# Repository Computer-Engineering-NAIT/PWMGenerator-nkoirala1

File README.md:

# PWMGenerator-nkoirala1
Practical Electronic - CMPE2150 - PCB Project

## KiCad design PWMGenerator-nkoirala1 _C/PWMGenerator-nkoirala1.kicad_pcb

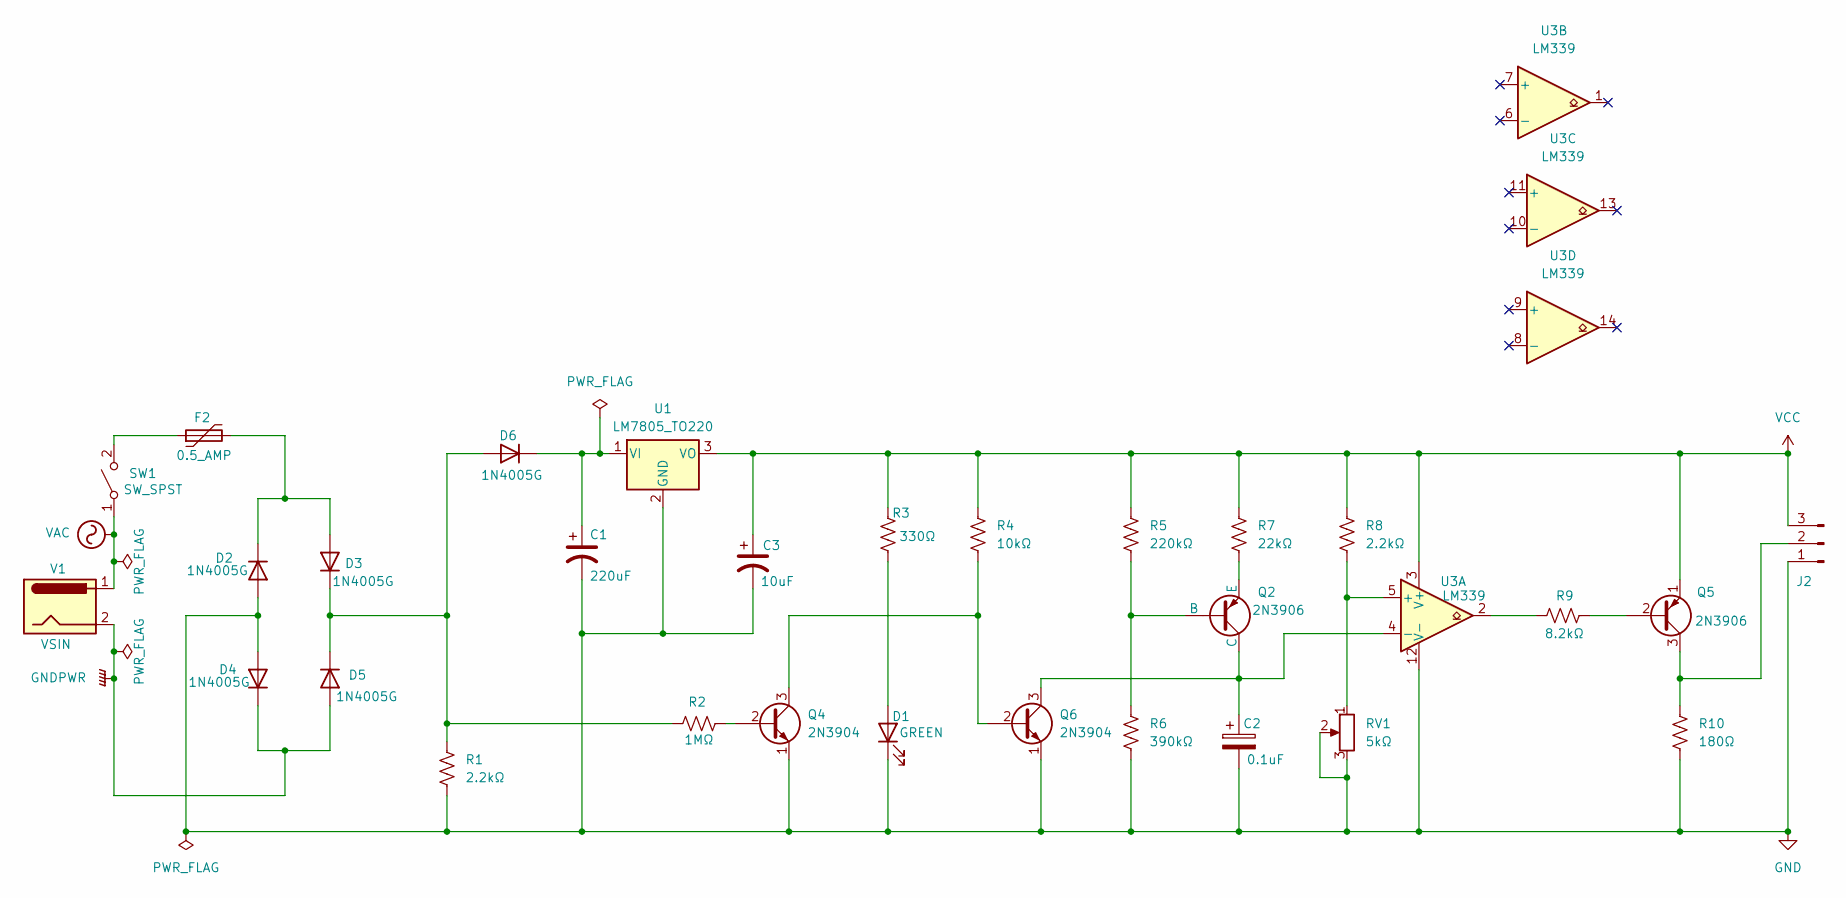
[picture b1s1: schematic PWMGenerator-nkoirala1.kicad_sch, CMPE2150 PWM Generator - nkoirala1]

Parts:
C1: 220uF; Wurth_Elektronik_220uf
C2: 0.1uF; C_0805_2012Metric
C3: 10uF; Wurth_Elektronik_10uf
D1: GREEN; LED_D5.0mm
D2, D3, D4, D5, D6: 1N4005G; D_0805_2012Metric_Pad1.15x1.40mm_HandSolder
F2: 0.5_AMP; RESC3115X65N
J2: Conn_01x03_Pin; PinHeader_1x03_P2.54mm_Vertical
Q2, Q5: 2N3906; SOT-23
Q4, Q6: 2N3904; SOT-23
R1, R8: 2.2kΩ; R_0805_2012Metric_Pad1.20x1.40mm_HandSolder
R2: 1MΩ; R_0805_2012Metric_Pad1.20x1.40mm_HandSolder
R3: 330Ω; R_0805_2012Metric_Pad1.20x1.40mm_HandSolder
R4: 10kΩ; R_0805_2012Metric_Pad1.20x1.40mm_HandSolder
R5: 220kΩ; R_0805_2012Metric_Pad1.20x1.40mm_HandSolder
R6: 390kΩ; R_0805_2012Metric_Pad1.20x1.40mm_HandSolder
R7: 22kΩ; R_0805_2012Metric_Pad1.20x1.40mm_HandSolder
R9: 8.2kΩ; R_0805_2012Metric_Pad1.20x1.40mm_HandSolder
R10: 180Ω; R_0805_2012Metric_Pad1.20x1.40mm_HandSolder
RV1: 5kΩ; Potentiometer_Bourns_3296W_Vertical
SW1: SW_SPST; SW_DIP_SPSTx01_Slide_6.7x4.1mm_W6.73mm_P2.54mm_LowProfile_J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
U1: LM7805_TO220; TO-220-3_Vertical
U3: LM339; SOIC-14_3.9x8.7mm_P1.27mm
V1: VSIN; BarrelJack_CUI_PJ-063AH_Horizontal

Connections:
GND: C1.2, C2.2, C3.2, D1.1 (K), D2.2 (A), D4.2 (A), J2.1, Q4.1 (E), Q6.1 (E), R1.2, R6.2, R10.2, RV1.2, RV1.3, U1.2 (GND), U3.12 (V-)
GNDPWR: D4.1 (K), D5.2 (A), V1.2
unnamed: D1.2 (A), R3.2
unnamed: D2.1 (K), D3.2 (A), F2.2
unnamed: D3.1 (K), D5.1 (K), D6.2 (A), R1.1, R2.1
unnamed: C1.1, D6.1 (K), U1.1 (VI)
unnamed: J2.2, Q5.3 (C), R10.1
unnamed: Q2.2 (B), R5.2, R6.1
unnamed: C2.1, Q2.1 (C), Q6.3 (C), U3.4 (-)
unnamed: Q2.3 (E), R7.2
unnamed: Q4.2 (B), R2.2
unnamed: Q4.3 (C), Q6.2 (B), R4.2
unnamed: Q5.2 (B), R9.2
unnamed: R9.1, U3.2
unnamed: F2.1, SW1.2 (B)
unnamed: R8.2, RV1.1, U3.5 (+)
VAC: SW1.1 (A), V1.1
VCC: C3.1, J2.3, Q5.1 (E), R3.1, R4.1, R5.1, R7.1, R8.1, U1.3 (VO), U3.3 (V+)

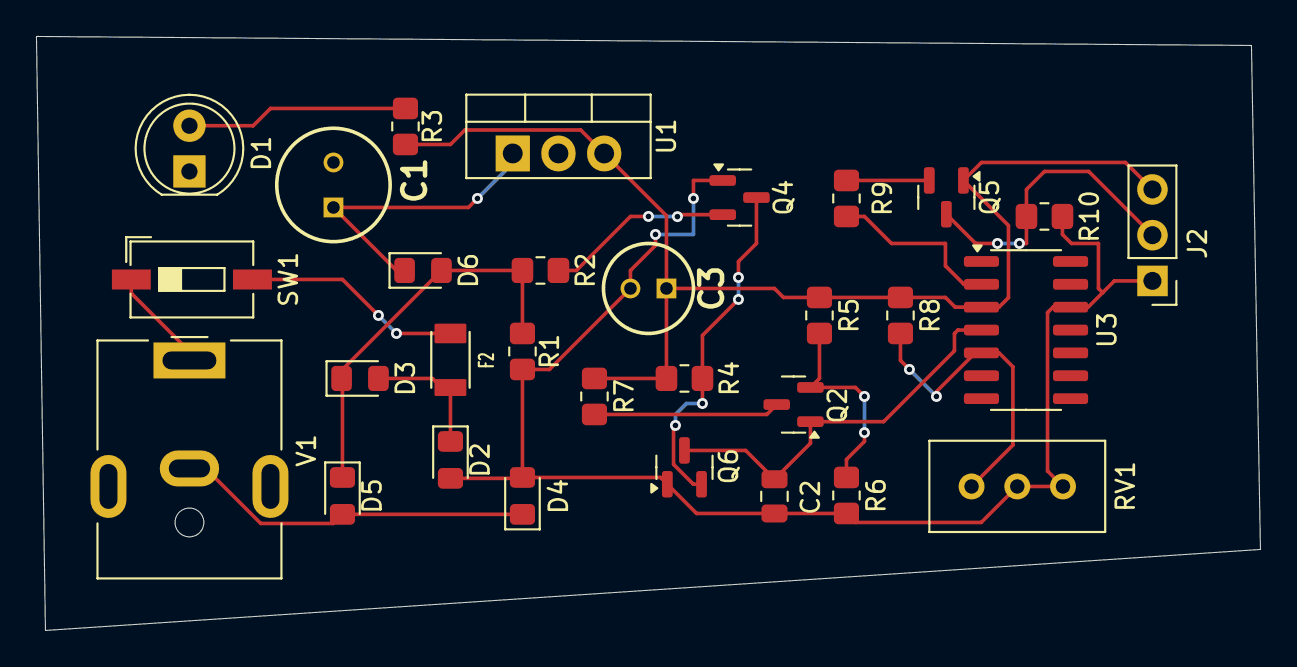
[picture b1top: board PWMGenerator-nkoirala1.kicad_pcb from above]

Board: 2 copper layers, 68.0 x 33.0 mm, 30 parts (0 on the bottom side), 18 nets.

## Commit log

2024-12-09 Project Created
    Part One project created and added the multisim for the whole schematic
2024-12-09 Deletion and recreating the project
    Forgot to include my name in the project
2024-12-09 Commit
    Finish the title block and auto back up
2024-12-09 Added Commponent
2024-12-09 placed all the components
    done
2024-12-09 commit wiring done
2024-12-10 for part B
2024-12-11 Resistors Footprint
    not potentiometer
2024-12-11 Capacity FootPrint
2024-12-11 Diode
    Including LED Done
2024-12-11 2N3904 And 2n3906
    Footprint
2024-12-11 Commit
    Fuse but its wrong need to do it
2024-12-11 commit
    added nano fuse
2024-12-15 commit
    tryma fix etc run error
2024-12-16 took a long time but its complete OArt B
    had wrong npn
2024-12-16 ommit started part c
    done with importing
2024-12-16 commit
    fixing some isses
2024-12-16 had my footprint wrong fr lm339
    Updated
2024-12-19 long long drags later
    finall one
2024-12-19 somehow done
    thank you
